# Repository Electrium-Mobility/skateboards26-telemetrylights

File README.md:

# Design

This is a mixed telemetry + lights board. We will use sensors (accelerometer) to gather information, a STM to process the info, and lights/display to display the result. Depending on the acceleration of the skateboard, the lights change to a different color. Data will also be displayed on a LCD/OLED screen.

Items displayed are:

* Acceleration
* Current/voltage draw of our board
* Precharge current sense
  * For the last two points, assume a separate power distribution board will be connected, and will be providing those signals through connectors.

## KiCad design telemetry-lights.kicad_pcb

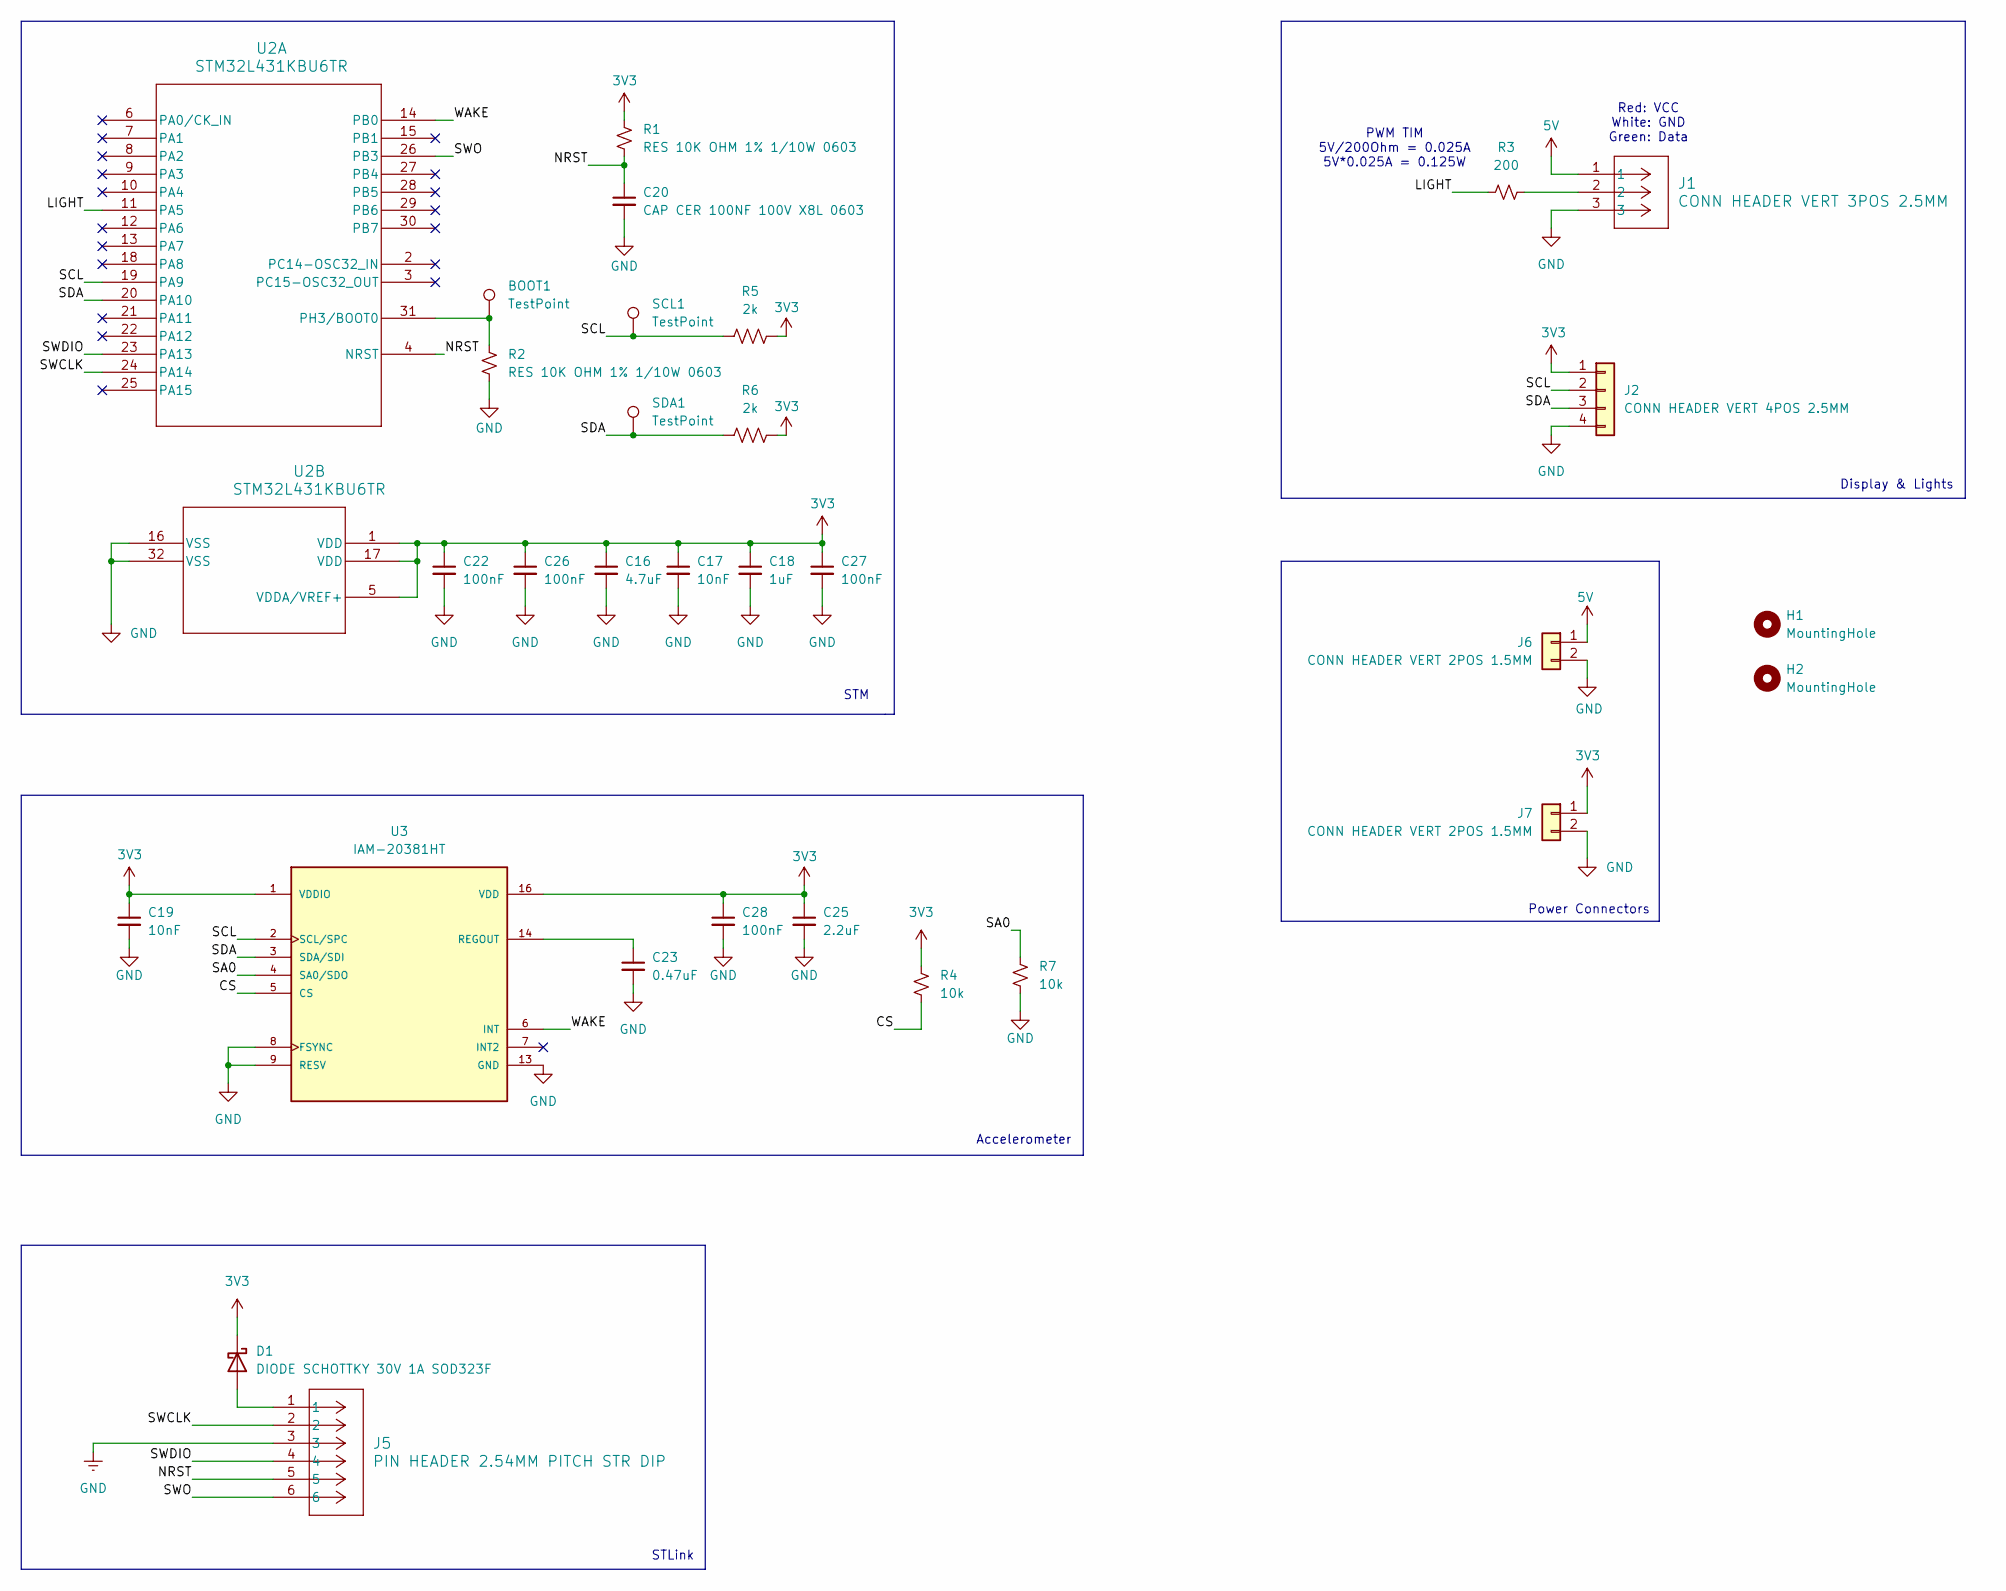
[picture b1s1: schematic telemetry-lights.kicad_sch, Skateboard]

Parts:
BOOT1: TestPoint; TestPoint_Pad_D1.0mm
C16: 4.7uF; C_0603_1608Metric
C17, C19: 10nF; C_0603_1608Metric
C18: 1uF; C_0603_1608Metric
C20: CAP CER 100NF 100V X8L 0603; C_0603_1608Metric
C22, C26, C27, C28: 100nF; C_0603_1608Metric
C23: 0.47uF; C_0603_1608Metric
C25: 2.2uF; C_0603_1608Metric
D1: DIODE SCHOTTKY 30V 1A SOD323F; P39_SOD-323P
H1, H2: MountingHole; MountingHole_2.5mm
J1: CONN HEADER VERT 3POS 2.5MM; CONN_B3B-XH-A_JST
J2: CONN HEADER VERT 4POS 2.5MM; JST_EH_B4B-EH-A_1x04_P2.50mm_Vertical
J5: PIN HEADER 2.54MM PITCH STR DIP; CONN6x1_G800W302018EU_AMP
J6, J7: CONN HEADER VERT 2POS 1.5MM; JST_ZH_B2B-ZR_1x02_P1.50mm_Vertical
R1, R2: RES 10K OHM 1% 1/10W 0603; R_0603_1608Metric
R3: 200; R_0603_1608Metric
R4, R7: 10k; R_0603_1608Metric
R5, R6: 2k; R_0603_1608Metric_Pad0.98x0.95mm_HandSolder
SCL1: TestPoint; TestPoint_Pad_D1.0mm
SDA1: TestPoint; TestPoint_Pad_D1.0mm
U2: STM32L431KBU6TR; UFQFPN-32
U3: IAM-20381HT; XDCR_IAM-20381HT; PARTREV 1.0

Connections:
3V3: C16.1, C17.1, C18.1, C19.1, C22.1, C25.1, C26.1, C27.1, C28.1, D1.1 (K), J2.1, J7.1, R1.1, R4.1, R5.2, R6.2, U2.1 (VDD), U2.5 (VDDA/VREF+), U2.17 (VDD), U3.1 (VDDIO), U3.16 (VDD)
5V: J1.1, J6.1
/CS: R4.2, U3.5 (CS)
/LIGHT: R3.1, U2.11 (PA5)
/NRST: C20.1, J5.5, R1.2, U2.4 (NRST)
/SA0: R7.1, U3.4 (SA0/SDO)
/SCL: J2.2, R5.1, SCL1.1 (1_1), U2.19 (PA9), U3.2 (SCL/SPC)
/SDA: J2.3, R6.1, SDA1.1 (1_1), U2.20 (PA10), U3.3 (SDA/SDI)
/SWCLK: J5.2, U2.24 (PA14)
/SWDIO: J5.4, U2.23 (PA13)
/SWO: J5.6, U2.26 (PB3)
/WAKE: U2.14 (PB0), U3.6 (INT)
GND: C16.2, C17.2, C18.2, C19.2, C20.2, C22.2, C23.2, C25.2, C26.2, C27.2, C28.2, J1.3, J2.4, J5.3, J6.2, J7.2, R2.2, R7.2, U2.16 (VSS), U2.32 (VSS), U3.8 (FSYNC), U3.9 (RESV), U3.10 (RESV), U3.11 (RESV), U3.12 (RESV), U3.13 (GND), U3.15 (RESV)
unnamed: D1.2 (A), J5.1
unnamed: J1.2, R3.2
unnamed 15: BOOT1.1, R2.1, U2.31 (PH3/BOOT0); also elsewhere on the board
unnamed: C23.1, U3.14 (REGOUT)

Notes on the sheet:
Accelerometer
PWM TIM 5V/200Ohm = 0.025A 5V*0.025A = 0.125W
Red: VCC White: GND Green: Data
STM
Display & Lights
STLink
Power Connectors

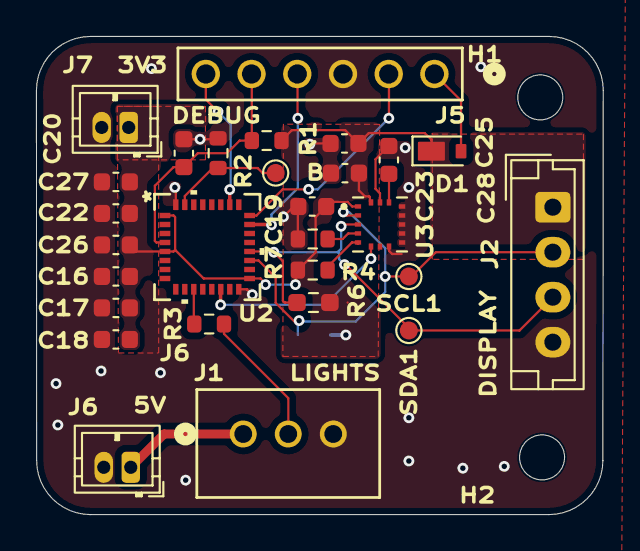
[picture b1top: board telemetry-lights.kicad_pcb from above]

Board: 2 copper layers, 31.5 x 26.6 mm, 31 parts (1 on the bottom side), 17 nets.

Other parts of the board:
B: TestPoint; TestPoint_Pad_D1.0mm

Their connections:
unnamed 15: B.1 (1_1); also elsewhere on the board

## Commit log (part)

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2026-06-09 Update README with project design and features
    Added project description and details about telemetry and lights functionality.
2026-06-14 Initialize KiCad project with empty custom symbol and footprint libraries
